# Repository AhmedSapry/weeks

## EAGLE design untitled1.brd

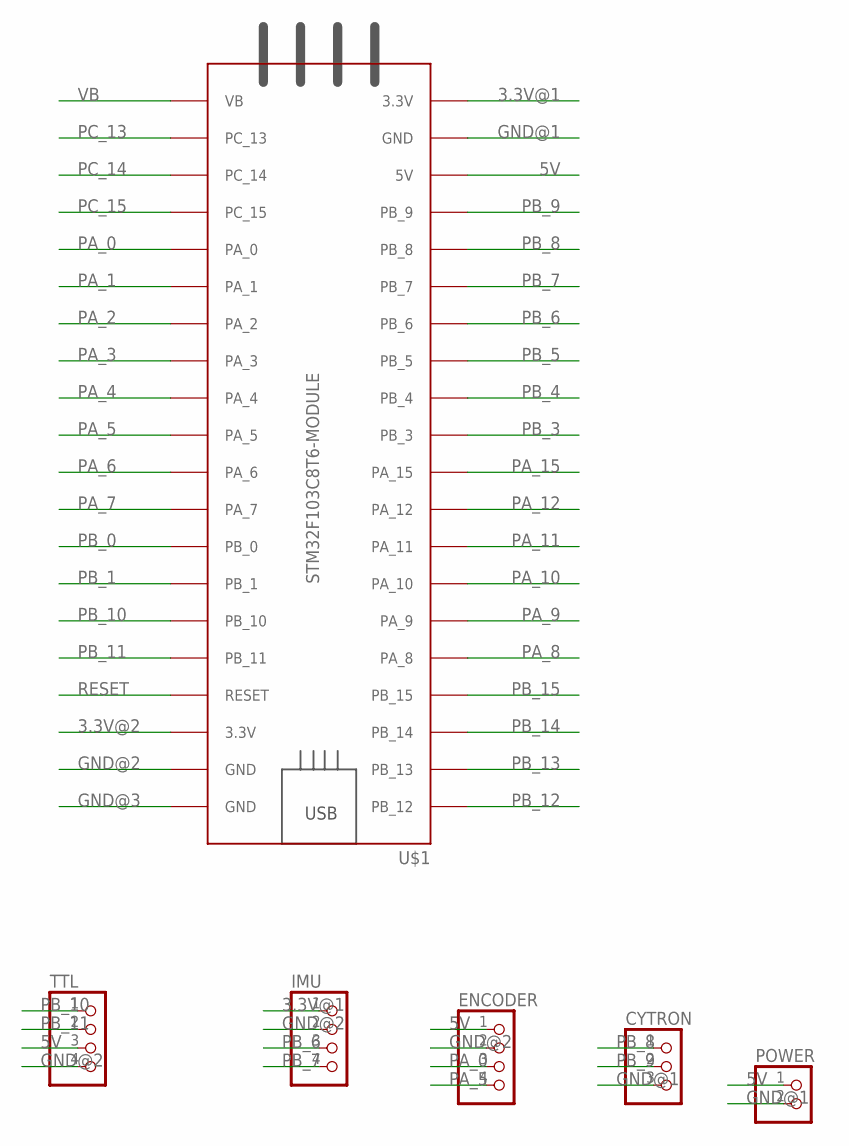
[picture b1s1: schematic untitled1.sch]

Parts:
CYTRON: PINHD-1X3; 1X03
ENCODER: PINHD-1X4; 1X04
IMU: PINHD-1X4; 1X04
POWER: PINHD-1X2; 1X02
TTL: PINHD-1X4; 1X04
U$1: STM32F103C8T6-MODULE

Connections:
3.3V@1: IMU.1, U$1.3.3V_1 (3.3V)
3.3V@2: U$1.3.3V_2 (3.3V)
5V: ENCODER.1, POWER.1, TTL.3, U$1.5V
GND@1: CYTRON.3, POWER.2, U$1.GND_1 (GND)
GND@2: ENCODER.2, IMU.2, TTL.4, U$1.GND_2 (GND)
GND@3: U$1.GND_3 (GND)
PA_0: ENCODER.3, U$1.PA_0
PA_1: U$1.PA_1
PA_2: U$1.PA_2
PA_3: U$1.PA_3
PA_4: U$1.PA_4
PA_5: ENCODER.4, U$1.PA_5
PA_6: U$1.PA_6
PA_7: U$1.PA_7
PA_8: U$1.PA_8
PA_9: U$1.PA_9
PA_10: U$1.PA_10
PA_11: U$1.PA_11
PA_12: U$1.PA_12
PA_15: U$1.PA_15
PB_0: U$1.PB_0
PB_1: U$1.PB_1
PB_3: U$1.PB_3
PB_4: U$1.PB_4
PB_5: U$1.PB_5
PB_6: IMU.3, U$1.PB_6
PB_7: IMU.4, U$1.PB_7
PB_8: CYTRON.1, U$1.PB_8
PB_9: CYTRON.2, U$1.PB_9
PB_10: TTL.1, U$1.PB_10
PB_11: TTL.2, U$1.PB_11
PB_12: U$1.PB_12
PB_13: U$1.PB_13
PB_14: U$1.PB_14
PB_15: U$1.PB_15
PC_13: U$1.PC_13
PC_14: U$1.PC_14
PC_15: U$1.PC_15
RESET: U$1.RESET
VB: U$1.VB

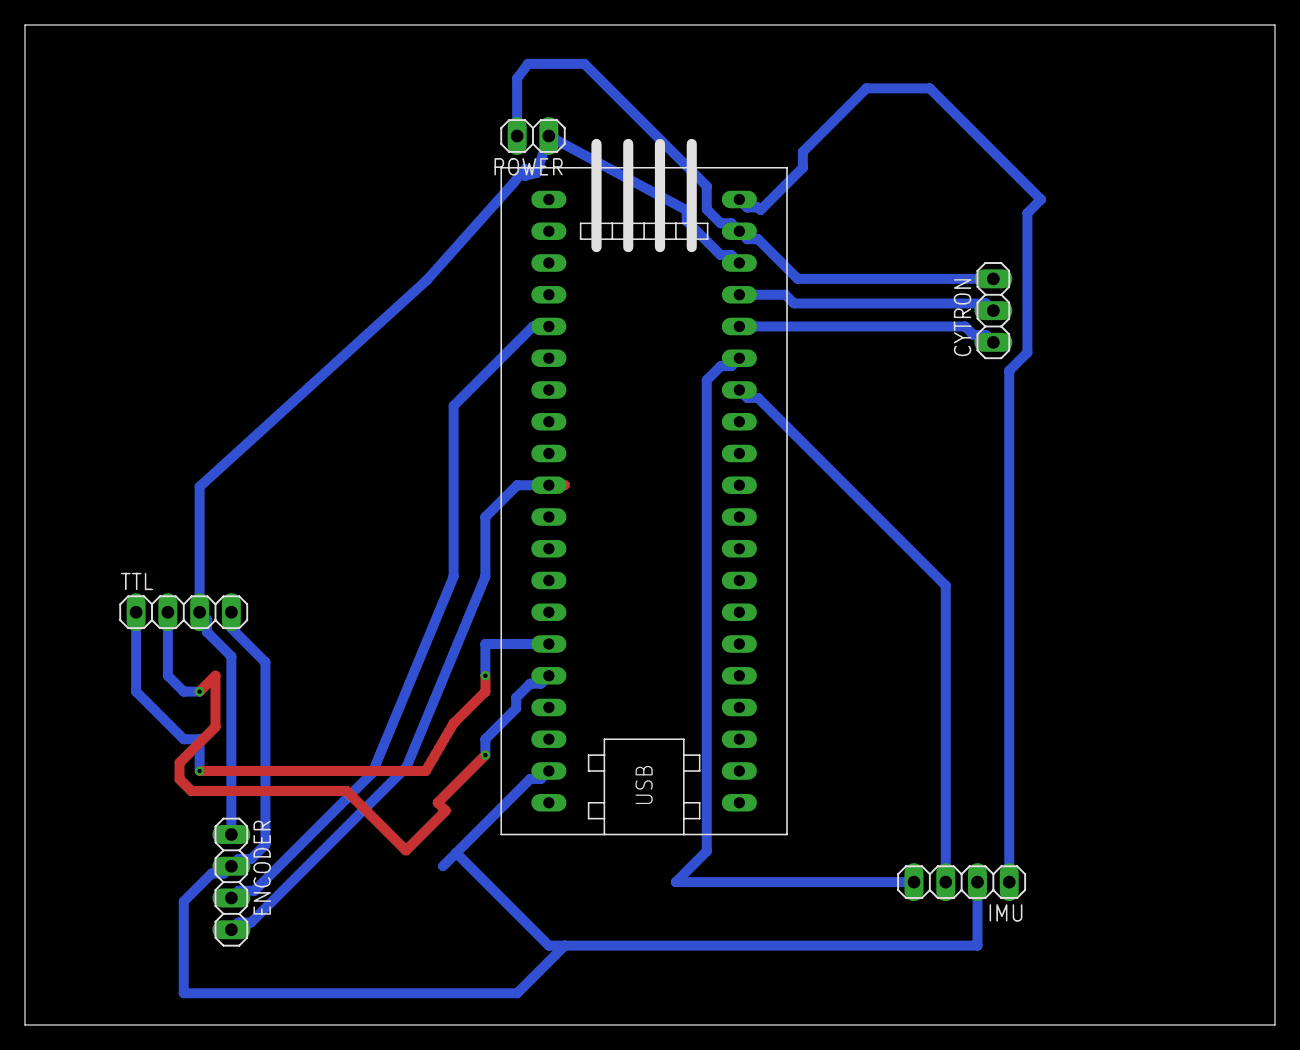
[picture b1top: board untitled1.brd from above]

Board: 2 copper layers, 100.0 x 80.0 mm, 6 parts (0 on the bottom side), 12 nets.
